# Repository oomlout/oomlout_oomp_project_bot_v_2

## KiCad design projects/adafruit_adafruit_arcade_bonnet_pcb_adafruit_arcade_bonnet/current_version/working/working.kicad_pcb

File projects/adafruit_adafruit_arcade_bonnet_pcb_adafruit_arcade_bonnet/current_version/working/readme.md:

# adafruit_arcade_bonnet_pcb
 
## summary 
* id: adafruit_adafruit_arcade_bonnet_pcb_adafruit_arcade_bonnet
* user: adafruit
* name: adafruit_arcade_bonnet_pcb
* board: adafruit_arcade_bonnet
* repo: https://github.com/adafruit/Adafruit-Arcade-Bonnet-PCB

* src_file_repo_sch: 
* src_file_repo_sch_link: https://github.com/adafruit/Adafruit-Arcade-Bonnet-PCB/tree/master/
* full details link: https://github.com/oomlout/oomlout_oomp_project_bot_v_2/tree/main/projects/adafruit_adafruit_arcade_bonnet_pcb_adafruit_arcade_bonnet/current_version/working  

## schematic  
  
[schematic (pdf)](working_schematic.pdf) 

## pcb  

[board (pdf)](working.pdf)  

## working_bom
| Id | Designator | Footprint | Quantity | Designation | Supplier and ref |  | None | 
| --- | --- | --- | --- | --- | --- | --- | --- | 
| 1 | U$11 | PCBFEAT-REV-040 | 1 |  |  |  | [''] | 
| 2 | B4,B3,B0,B5,B2,B1 | JST-XH-2-SM4 | 6 | CON_JST_XH_2PIN-SM4 |  |  | [''] | 
| 3 | R3,R2 | 0805-NO | 2 | 10K |  |  | [''] | 
| 4 | U1 | QFN16_3MM | 1 | MAX98357A |  |  | [''] | 
| 5 | JP8,JP9,JP10,JP7,JP4,JP6 | 1X02_OVAL | 6 |  |  |  | [''] | 
| 6 | RPI1 | PI_BONNET | 1 | RASPBERRYPI_BPLUS_PHAT |  |  | [''] | 
| 7 | R4 | 0603-NO | 1 | 1M |  |  | [''] | 
| 8 | JP2,JP3 | 1X03_ROUND | 2 |  |  |  | [''] | 
| 9 | IC1 | QFN28-ML_6X6MM | 1 | MCP23017ML |  |  | [''] | 
| 10 | SPKR0 | TERMBLOCK_1X2-3.5MM | 1 | 3.5mm |  |  | [''] | 
| 11 | FID2,FID3 | FIDUCIAL_1MM | 2 | FIDUCIAL" |  |  | [''] | 
| 12 | R1 | 0805_10MGAP | 1 | 10K |  |  | [''] | 
| 13 | JP1 | 1X04_OVAL | 1 |  |  |  | [''] | 
| 14 | D1 | CHIPLED_0805_NOOUTLINE | 1 | red |  |  | [''] | 
| 15 | R5 | 0603-NO | 1 | 1K |  |  | [''] | 
| 16 | IC2 | TSSOP14 | 1 | LM339P |  |  | [''] | 
| 17 | U$19 | BONNET_ARCADE_REVB_TOP | 1 |  |  |  | [''] | 
| 18 | C2 | 0805-NO | 1 | 10uF |  |  | [''] | 
| 19 | JOY1 | 1X05_OVAL | 1 |  |  |  | [''] | 
| 20 | C1 | 0603-NO | 1 | 0.1uF |  |  | [''] | 
| 21 | CONN1 | 1X25_ROUND_70MIL | 1 | HEADER-1X25 |  |  | [''] | 
| 22 | SJ1 | SOLDERJUMPER_2WAY_OPEN_NOPASTE | 1 | ADDR |  |  | [''] | 
| 23 | U$20 | BONNET_ARCADE_REVB_BOT | 1 |  |  |  | [''] | 
| 24 | SJ2 | SOLDERJUMPER_CLOSEDWIRE | 1 |  |  |  | [''] | 

## bom_schematic
| Ref | Qnty | Value | Cmp name | Footprint | Description | Vendor | DNP | 
| --- | --- | --- | --- | --- | --- | --- | --- | 
| B0, B1, B2, B3, B4, B5 | 6 | CON_JST_XH_2PIN-SM4 | CON_JST_XH_2PIN-SM4 | working:JST-XH-2-SM4 |  |  |  | 
| C1 | 1 | 0.1uF | CAP_CERAMIC0603_NO | working:0603-NO |  |  |  | 
| C2 | 1 | 10uF | CAP_CERAMIC0805-NOOUTLINE | working:0805-NO |  |  |  | 
| CONN1 | 1 | HEADER-1X25 | HEADER-1X25 | working:1X25_ROUND_70MIL |  |  |  | 
| D1 | 1 | red | LED0805_NOOUTLINE | working:CHIPLED_0805_NOOUTLINE |  |  |  | 
| FID2, FID3 | 2 | FIDUCIAL"" | FIDUCIAL{dblquote}{dblquote} | working:FIDUCIAL_1MM |  |  |  | 
| IC1 | 1 | MCP23017ML | MCP23017ML | working:QFN28-ML_6X6MM |  |  |  | 
| IC2 | 1 | LM339P | LM339P | working:TSSOP14 |  |  |  | 
| JOY1 | 1 | HEADER-1X5 | HEADER-1X5 | working:1X05_OVAL |  |  |  | 
| JP1 | 1 | HEADER-1X4 | HEADER-1X4 | working:1X04_OVAL |  |  |  | 
| JP2, JP3 | 2 | HEADER-1X3ROUND | HEADER-1X3ROUND | working:1X03_ROUND |  |  |  | 
| JP4, JP6, JP7, JP8, JP9, JP10 | 6 | HEADER-1X2 | HEADER-1X2 | working:1X02_OVAL |  |  |  | 
| R1 | 1 | 10K | RESISTOR0805_10MGAP | working:0805_10MGAP |  |  |  | 
| R2, R3 | 2 | 10K | RESISTOR0805_NOOUTLINE | working:0805-NO |  |  |  | 
| R4 | 1 | 1M | RESISTOR_0603_NOOUT | working:0603-NO |  |  |  | 
| R5 | 1 | 1K | RESISTOR_0603_NOOUT | working:0603-NO |  |  |  | 
| RPI1 | 1 | RASPBERRYPI_BPLUS_PHAT | RASPBERRYPI_BPLUS_PHAT | working:PI_BONNET |  |  |  | 
| SJ1 | 1 | ADDR | SOLDERJUMPER_2WAY | working:SOLDERJUMPER_2WAY_OPEN_NOPASTE |  |  |  | 
| SJ2 | 1 | SOLDERJUMPERCLOSED | SOLDERJUMPERCLOSED | working:SOLDERJUMPER_CLOSEDWIRE |  |  |  | 
| SPKR0 | 1 | 3.5mm | TERMBLOCK_1X2 | working:TERMBLOCK_1X2-3.5MM |  |  |  | 
| U1 | 1 | MAX98357A | AUDIOAMP_MAX98357 | working:QFN16_3MM |  |  |  |

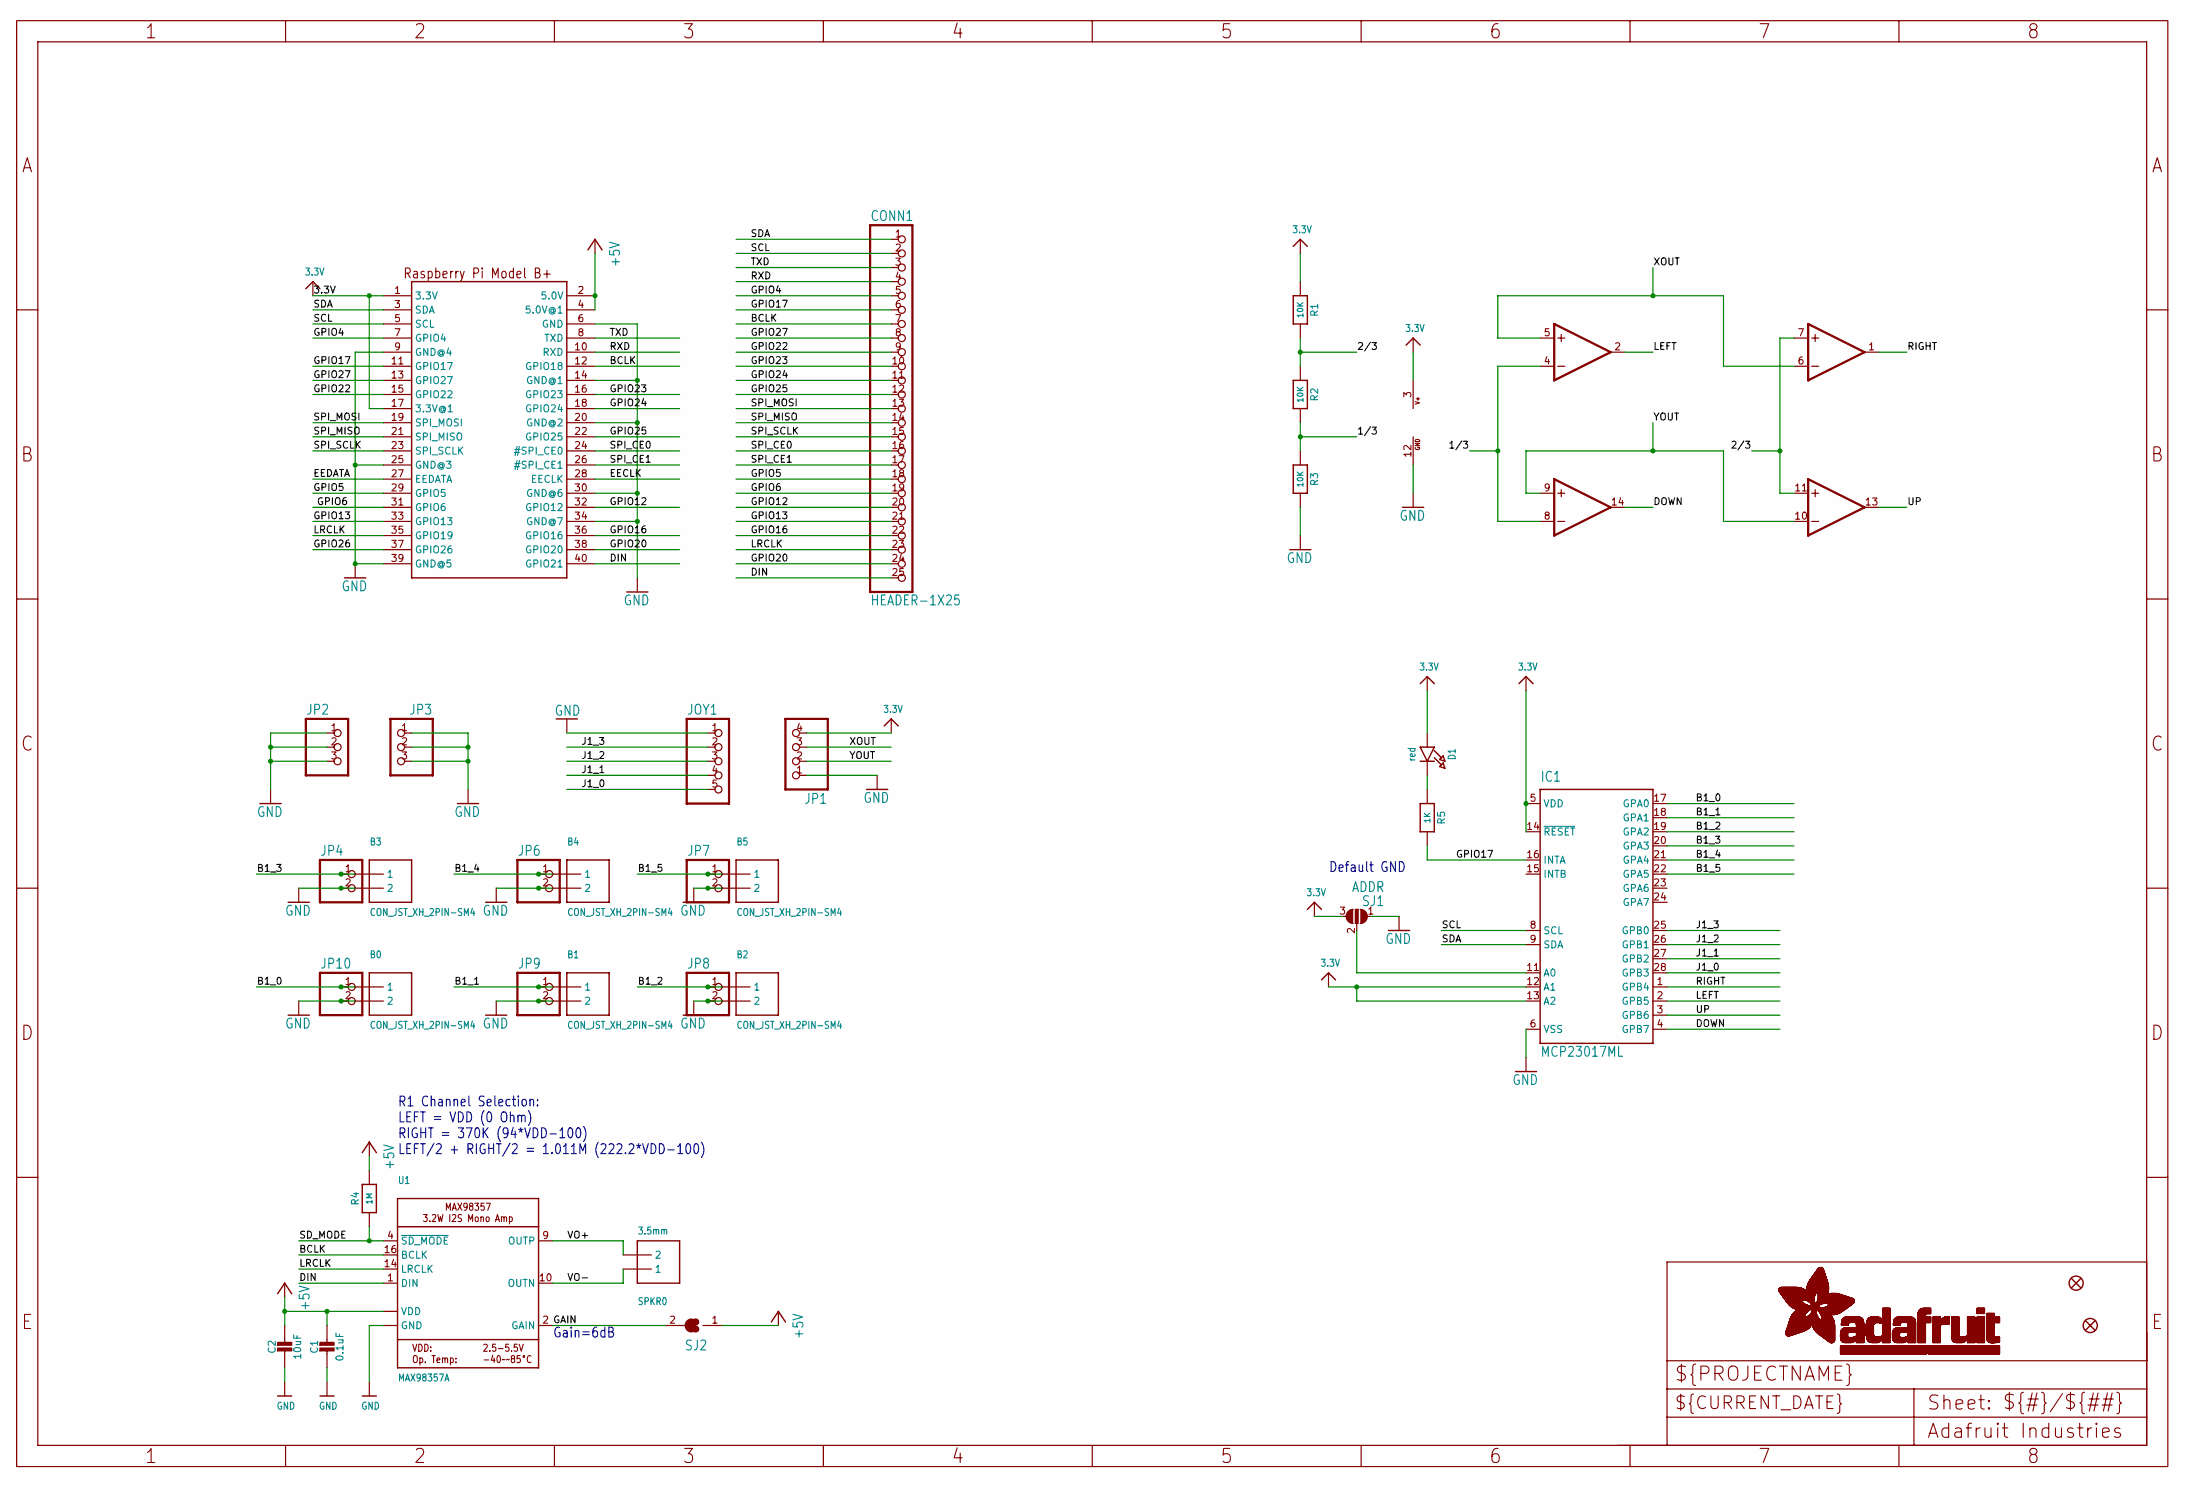
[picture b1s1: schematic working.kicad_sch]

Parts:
B0, B1, B2, B3, B4, B5: CON_JST_XH_2PIN-SM4; JST-XH-2-SM4
C1: 0.1uF; 0603-NO
C2: 10uF; 0805-NO
CONN1: HEADER-1X25; 1X25_ROUND_70MIL
D1: red; CHIPLED_0805_NOOUTLINE
FID2, FID3: FIDUCIAL""; FIDUCIAL_1MM
IC1: MCP23017ML; QFN28-ML_6X6MM; MPN MCP23017-E/SS
IC2: LM339P; TSSOP14
JOY1: HEADER-1X5; 1X05_OVAL
JP1: HEADER-1X4; 1X04_OVAL
JP2, JP3: HEADER-1X3ROUND; 1X03_ROUND
JP4, JP6, JP7, JP8, JP9, JP10: HEADER-1X2; 1X02_OVAL
R1: 10K; 0805_10MGAP
R2, R3: 10K; 0805-NO
R4: 1M; 0603-NO
R5: 1K; 0603-NO
RPI1: RASPBERRYPI_BPLUS_PHAT; PI_BONNET
SJ1: ADDR; SOLDERJUMPER_2WAY_OPEN_NOPASTE
SJ2: SOLDERJUMPERCLOSED; SOLDERJUMPER_CLOSEDWIRE
SPKR0: 3.5mm; TERMBLOCK_1X2-3.5MM
U1: MAX98357A; QFN16_3MM

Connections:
1/3: IC2.4 (-IN), IC2.8 (-IN), R2.2, R3.1
2/3: IC2.7 (+IN), IC2.11 (+IN), R1.2, R2.1
3.3V: D1.A, IC1.5 (VDD), IC1.12 (A1), IC1.13 (A2), IC1.14 (~RESET), IC2.3 (V+), JP1.4, R1.1, RPI1.1 (3.3V), RPI1.17 (3.3V@1), SJ1.3
+5V: C1.1, C2.1, R4.2, RPI1.2 (5.0V), RPI1.4 (5.0V@1), SJ2.1, U1.7 (VDD), U1.8 (VDD)
B1_0: B0.1, IC1.17 (GPA0), JP10.1
B1_1: B1.1, IC1.18 (GPA1), JP9.1
B1_2: B2.1, IC1.19 (GPA2), JP8.1
B1_3: B3.1, IC1.20 (GPA3), JP4.1
B1_4: B4.1, IC1.21 (GPA4), JP6.1
B1_5: B5.1, IC1.22 (GPA5), JP7.1
BCLK: CONN1.7, RPI1.12 (GPIO18), U1.16 (BCLK)
DIN: CONN1.25, RPI1.40 (GPIO21), U1.1 (DIN)
DOWN: IC1.4 (GPB7), IC2.14 (OUT)
EECLK: RPI1.28 (EECLK)
EEDATA: RPI1.27 (EEDATA)
GAIN: SJ2.2, U1.2 (GAIN)
GND: B0.2, B1.2, B2.2, B3.2, B4.2, B5.2, C1.2, C2.2, IC1.6 (VSS), IC2.12 (GND), JOY1.1, JP1.1, JP2.1, JP2.2, JP2.3, JP3.1, JP3.2, JP3.3, JP4.2, JP6.2, JP7.2, JP8.2, JP9.2, JP10.2, R3.2, RPI1.6 (GND), RPI1.9 (GND@4), RPI1.14 (GND@1), RPI1.20 (GND@2), RPI1.25 (GND@3), RPI1.30 (GND@6), RPI1.34 (GND@7), RPI1.39 (GND@5), SJ1.1, U1.3 (GND), U1.11 (GND), U1.15 (GND), U1.THERMAL (GND)
GPIO4: CONN1.5, RPI1.7 (GPIO4)
GPIO5: CONN1.18, RPI1.29 (GPIO5)
GPIO6: CONN1.19, RPI1.31 (GPIO6)
GPIO12: CONN1.20, RPI1.32 (GPIO12)
GPIO13: CONN1.21, RPI1.33 (GPIO13)
GPIO16: CONN1.22, RPI1.36 (GPIO16)
GPIO17: CONN1.6, IC1.16 (INTA), R5.2, RPI1.11 (GPIO17)
GPIO20: CONN1.24, RPI1.38 (GPIO20)
GPIO22: CONN1.9, RPI1.15 (GPIO22)
GPIO23: CONN1.10, RPI1.16 (GPIO23)
GPIO24: CONN1.11, RPI1.18 (GPIO24)
GPIO25: CONN1.12, RPI1.22 (GPIO25)
GPIO26: RPI1.37 (GPIO26)
GPIO27: CONN1.8, RPI1.13 (GPIO27)
J1_0: IC1.28 (GPB3), JOY1.5
J1_1: IC1.27 (GPB2), JOY1.4
J1_2: IC1.26 (GPB1), JOY1.3
J1_3: IC1.25 (GPB0), JOY1.2
LEFT: IC1.2 (GPB5), IC2.2 (OUT)
LRCLK: CONN1.23, RPI1.35 (GPIO19), U1.14 (LRCLK)
unnamed: IC1.11 (A0), SJ1.2
unnamed: D1.C, R5.1
RIGHT: IC1.1 (GPB4), IC2.1 (OUT)
RXD: CONN1.4, RPI1.10 (RXD)
SCL: CONN1.2, IC1.8 (SCL), RPI1.5 (SCL)
SDA: CONN1.1, IC1.9 (SDA), RPI1.3 (SDA)
SD_MODE: R4.1, U1.4 (~SD_MODE)
SPI_CE0: CONN1.16, RPI1.24 (#SPI_CE0)
SPI_CE1: CONN1.17, RPI1.26 (#SPI_CE1)
SPI_MISO: CONN1.14, RPI1.21 (SPI_MISO)
SPI_MOSI: CONN1.13, RPI1.19 (SPI_MOSI)
SPI_SCLK: CONN1.15, RPI1.23 (SPI_SCLK)
TXD: CONN1.3, RPI1.8 (TXD)
UP: IC1.3 (GPB6), IC2.13 (OUT)
VO+: SPKR0.2, U1.9 (OUTP)
VO-: SPKR0.1, U1.10 (OUTN)
XOUT: IC2.5 (+IN), IC2.6 (-IN), JP1.3
YOUT: IC2.9 (+IN), IC2.10 (-IN), JP1.2

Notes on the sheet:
Default GND
R1 Channel Selection: LEFT = VDD (0 Ohm) RIGHT = 370K (94*VDD-100) LEFT/2 + RIGHT/2 = 1.011M (222.2*VDD-100)
Gain=6dB

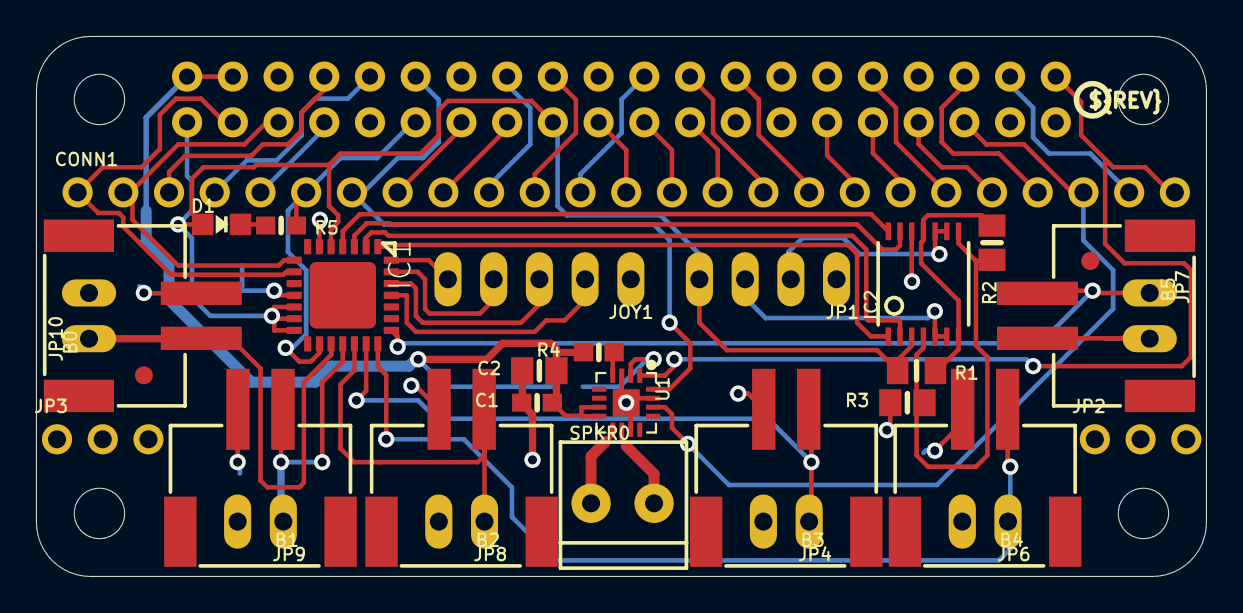
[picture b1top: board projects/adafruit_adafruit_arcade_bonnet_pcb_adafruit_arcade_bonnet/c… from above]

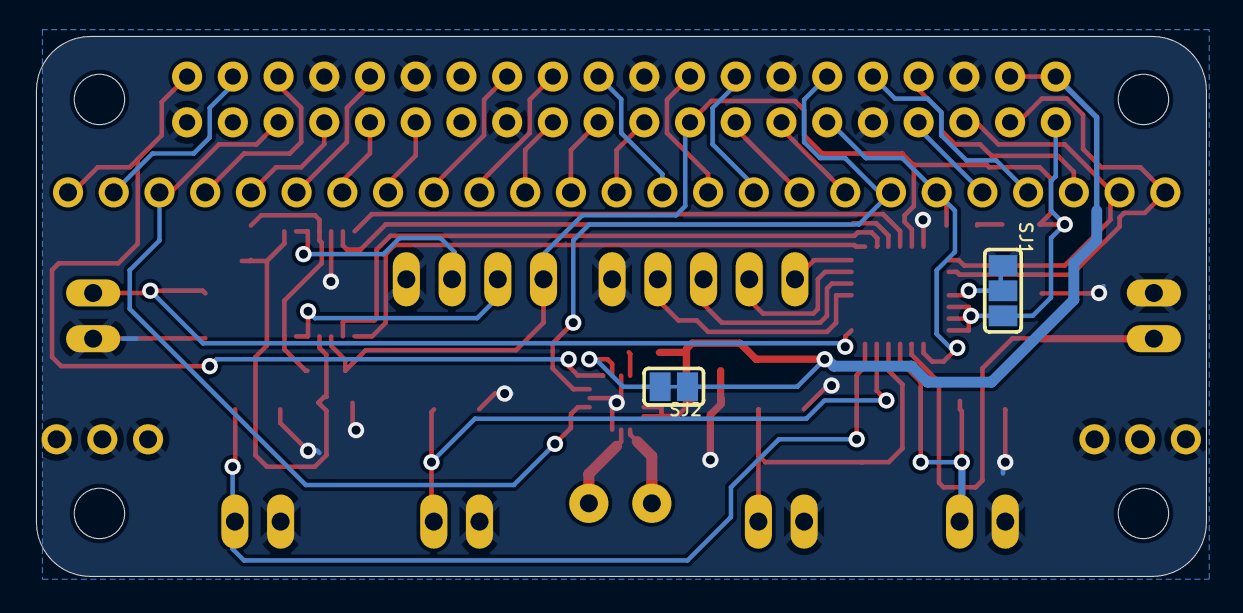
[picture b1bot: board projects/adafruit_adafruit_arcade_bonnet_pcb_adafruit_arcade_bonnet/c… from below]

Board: 2 copper layers, 65.0 x 30.0 mm, 37 parts (3 on the bottom side), 52 nets.

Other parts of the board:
U$11: PCBFEAT-REV-040
U$19: BONNET_ARCADE_REVB_TOP
U$20: BONNET_ARCADE_REVB_BOT

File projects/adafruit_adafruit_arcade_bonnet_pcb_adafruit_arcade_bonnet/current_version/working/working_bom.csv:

"Id";"Designator";"Footprint";"Quantity";"Designation";"Supplier and ref";
1;"U$11";"PCBFEAT-REV-040";1;"";;;
2;"B4,B3,B0,B5,B2,B1";"JST-XH-2-SM4";6;"CON_JST_XH_2PIN-SM4";;;
3;"R3,R2";"0805-NO";2;"10K";;;
4;"U1";"QFN16_3MM";1;"MAX98357A";;;
5;"JP8,JP9,JP10,JP7,JP4,JP6";"1X02_OVAL";6;"";;;
6;"RPI1";"PI_BONNET";1;"RASPBERRYPI_BPLUS_PHAT";;;
7;"R4";"0603-NO";1;"1M";;;
8;"JP2,JP3";"1X03_ROUND";2;"";;;
9;"IC1";"QFN28-ML_6X6MM";1;"MCP23017ML";;;
10;"SPKR0";"TERMBLOCK_1X2-3.5MM";1;"3.5mm";;;
11;"FID2,FID3";"FIDUCIAL_1MM";2;"FIDUCIAL""";;;
12;"R1";"0805_10MGAP";1;"10K";;;
13;"JP1";"1X04_OVAL";1;"";;;
14;"D1";"CHIPLED_0805_NOOUTLINE";1;"red";;;
15;"R5";"0603-NO";1;"1K";;;
16;"IC2";"TSSOP14";1;"LM339P";;;
17;"U$19";"BONNET_ARCADE_REVB_TOP";1;"";;;
18;"C2";"0805-NO";1;"10uF";;;
19;"JOY1";"1X05_OVAL";1;"";;;
20;"C1";"0603-NO";1;"0.1uF";;;
21;"CONN1";"1X25_ROUND_70MIL";1;"HEADER-1X25";;;
22;"SJ1";"SOLDERJUMPER_2WAY_OPEN_NOPASTE";1;"ADDR";;;
23;"U$20";"BONNET_ARCADE_REVB_BOT";1;"";;;
24;"SJ2";"SOLDERJUMPER_CLOSEDWIRE";1;"";;;

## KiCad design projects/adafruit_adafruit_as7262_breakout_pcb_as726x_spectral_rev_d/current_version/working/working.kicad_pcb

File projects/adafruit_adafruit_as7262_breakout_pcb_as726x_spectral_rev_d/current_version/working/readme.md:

# adafruit_as7262_breakout_pcb
 
## summary 
* id: adafruit_adafruit_as7262_breakout_pcb_as726x_spectral_rev_d
* user: adafruit
* name: adafruit_as7262_breakout_pcb
* board: as726x_spectral_rev_d
* repo: https://github.com/adafruit/Adafruit-AS7262-Breakout-PCB

* src_file_repo_sch: 
* src_file_repo_sch_link: https://github.com/adafruit/Adafruit-AS7262-Breakout-PCB/tree/master/
* full details link: https://github.com/oomlout/oomlout_oomp_project_bot_v_2/tree/main/projects/adafruit_adafruit_as7262_breakout_pcb_as726x_spectral_rev_d/current_version/working  

## schematic  
  
[schematic (pdf)](working_schematic.pdf) 

## pcb  

[board (pdf)](working.pdf)  

## working_bom
| Id | Designator | Footprint | Quantity | Designation | Supplier and ref |  | None | 
| --- | --- | --- | --- | --- | --- | --- | --- | 
| 1 | U$2,U$22,U$3,U$23 | MOUNTINGHOLE_2.5_PLATED | 4 | MOUNTINGHOLE2.5 |  |  | [''] | 
| 2 | U$25 | SYMBOL_PLUS | 1 |  |  |  | [''] | 
| 3 | R2 | 0805-NO | 1 | 10K |  |  | [''] | 
| 4 | D1 | EVERLIGHT_45-21 | 1 | L130-5780001400001 |  |  | [''] | 
| 5 | U2 | AS726X_LGA20 | 1 | AS7262-BLGT |  |  | [''] | 
| 6 | R8 | RESPACK_4X0603_NO | 1 | 10k |  |  | [''] | 
| 7 | EXT_LED0 | 1X02_ROUND | 1 |  |  |  | [''] | 
| 8 | C3,C1,C2 | 0805-NO | 3 | 10uF |  |  | [''] | 
| 9 | UART0 | SOLDERJUMPER_ARROW_NOPASTE | 1 |  |  |  | [''] | 
| 10 | R7 | 0603-NO | 1 | 10K |  |  | [''] | 
| 11 | C4,C5 | 0603-NO | 2 | 0.1uF |  |  | [''] | 
| 12 | Q3 | SOT363 | 1 | BSS138 |  |  | [''] | 
| 13 | D2 | CHIPLED_0805_NOOUTLINE | 1 | GREEN |  |  | [''] | 
| 14 | U3 | SOT23-5 | 1 | MIC5225-3.3 |  |  | [''] | 
| 15 | U1 | SOIC8_150MIL | 1 | AT25SF041-SSHD-B |  |  | [''] | 
| 16 | FID3,FID2 | FIDUCIAL_1MM | 2 | FIDUCIAL_1MM |  |  | [''] | 
| 17 | JP2,FTDI1 | 1X07_ROUND | 2 |  |  |  | [''] | 
| 18 | U$26 | SYMBOL_MINUS | 1 |  |  |  | [''] | 
| 19 | D3 | SOD-323 | 1 | IN4148 |  |  | [''] | 
| 20 | U$21 | ADAFRUIT_2.5MM | 1 |  |  |  | [''] | 
| 21 | TP1,TP3,TP2,TP4 | TP15R | 4 | PTR1TP15R |  |  | [''] | 
| 22 | U$9 | ADAFRUIT_5MM | 1 |  |  |  | [''] | 
| 23 | LED0 | SOLDERJUMPER_CLOSEDWIRE | 1 |  |  |  | [''] | 

## bom_schematic
| Ref | Qnty | Value | Cmp name | Footprint | Description | Vendor | DNP | 
| --- | --- | --- | --- | --- | --- | --- | --- | 
| C1, C2, C3 | 3 | 10uF | CAP_CERAMIC0805-NOOUTLINE | working:0805-NO |  |  |  | 
| C4, C5 | 2 | 0.1uF | CAP_CERAMIC0603_NO | working:0603-NO |  |  |  | 
| D1 | 1 | L130-5780001400001 | LEDEV45-21 | working:EVERLIGHT_45-21 |  |  |  | 
| D2 | 1 | GREEN | LED0805_NOOUTLINE | working:CHIPLED_0805_NOOUTLINE |  |  |  | 
| D3 | 1 | IN4148 | DIODESOD-323 | working:SOD-323 |  |  |  | 
| EXT_LED0 | 1 | HEADER-1X2ROUND | HEADER-1X2ROUND | working:1X02_ROUND |  |  |  | 
| FID2, FID3 | 2 | FIDUCIAL_1MM | FIDUCIAL_1MM | working:FIDUCIAL_1MM |  |  |  | 
| FTDI1 | 1 | HEADER-1X7ROUND | HEADER-1X7ROUND | working:1X07_ROUND |  |  |  | 
| JP2 | 1 | HEADER-1X7ROUND | HEADER-1X7ROUND | working:1X07_ROUND |  |  |  | 
| LED0 | 1 | SOLDERJUMPERCLOSED | SOLDERJUMPERCLOSED | working:SOLDERJUMPER_CLOSEDWIRE |  |  |  | 
| Q3 | 1 | BSS138 | MOSFET-N_DUAL | working:SOT363 |  |  |  | 
| R2 | 1 | 10K | RESISTOR0805_NOOUTLINE | working:0805-NO |  |  |  | 
| R7 | 1 | 10K | microbuilder_09_Nov_2015_RESISTOR_0603_NOOUT | working:0603-NO |  |  |  | 
| R8 | 1 | 10k | RESISTOR_4PACK_NO | working:RESPACK_4X0603_NO |  |  |  | 
| TP1, TP2, TP3, TP4 | 4 | PTR1TP15R | PTR1TP15R | working:TP15R |  |  |  | 
| U1 | 1 | AT25SF041-SSHD-B | SPIFLASH_SOIC8 | working:SOIC8_150MIL |  |  |  | 
| U2 | 1 | AS7262-BLGT | AS726X_SPECTRAL | working:AS726X_LGA20 |  |  |  | 
| U3 | 1 | MIC5225-3.3 | VREG_SOT23-5 | working:SOT23-5 |  |  |  | 
| U$2, U$3, U$22, U$23 | 4 | MOUNTINGHOLE2.5 | MOUNTINGHOLE2.5 | working:MOUNTINGHOLE_2.5_PLATED |  |  |  | 
| UART0 | 1 | SOLDERJUMPER | SOLDERJUMPER | working:SOLDERJUMPER_ARROW_NOPASTE |  |  |  | 

## mounting_holes
| x | y | package | value | ref | size | 
| --- | --- | --- | --- | --- | --- | 
| 22.86 | 0.0 | MOUNTINGHOLE_2.5_PLATED | MOUNTINGHOLE2.5 | U$2 | m3 | 
| 0.0 | 0.0 | MOUNTINGHOLE_2.5_PLATED | MOUNTINGHOLE2.5 | U$3 | m3 | 
| 22.86 | 20.32 | MOUNTINGHOLE_2.5_PLATED | MOUNTINGHOLE2.5 | U$22 | m3 | 
| 0.0 | 20.32 | MOUNTINGHOLE_2.5_PLATED | MOUNTINGHOLE2.5 | U$23 | m3 |

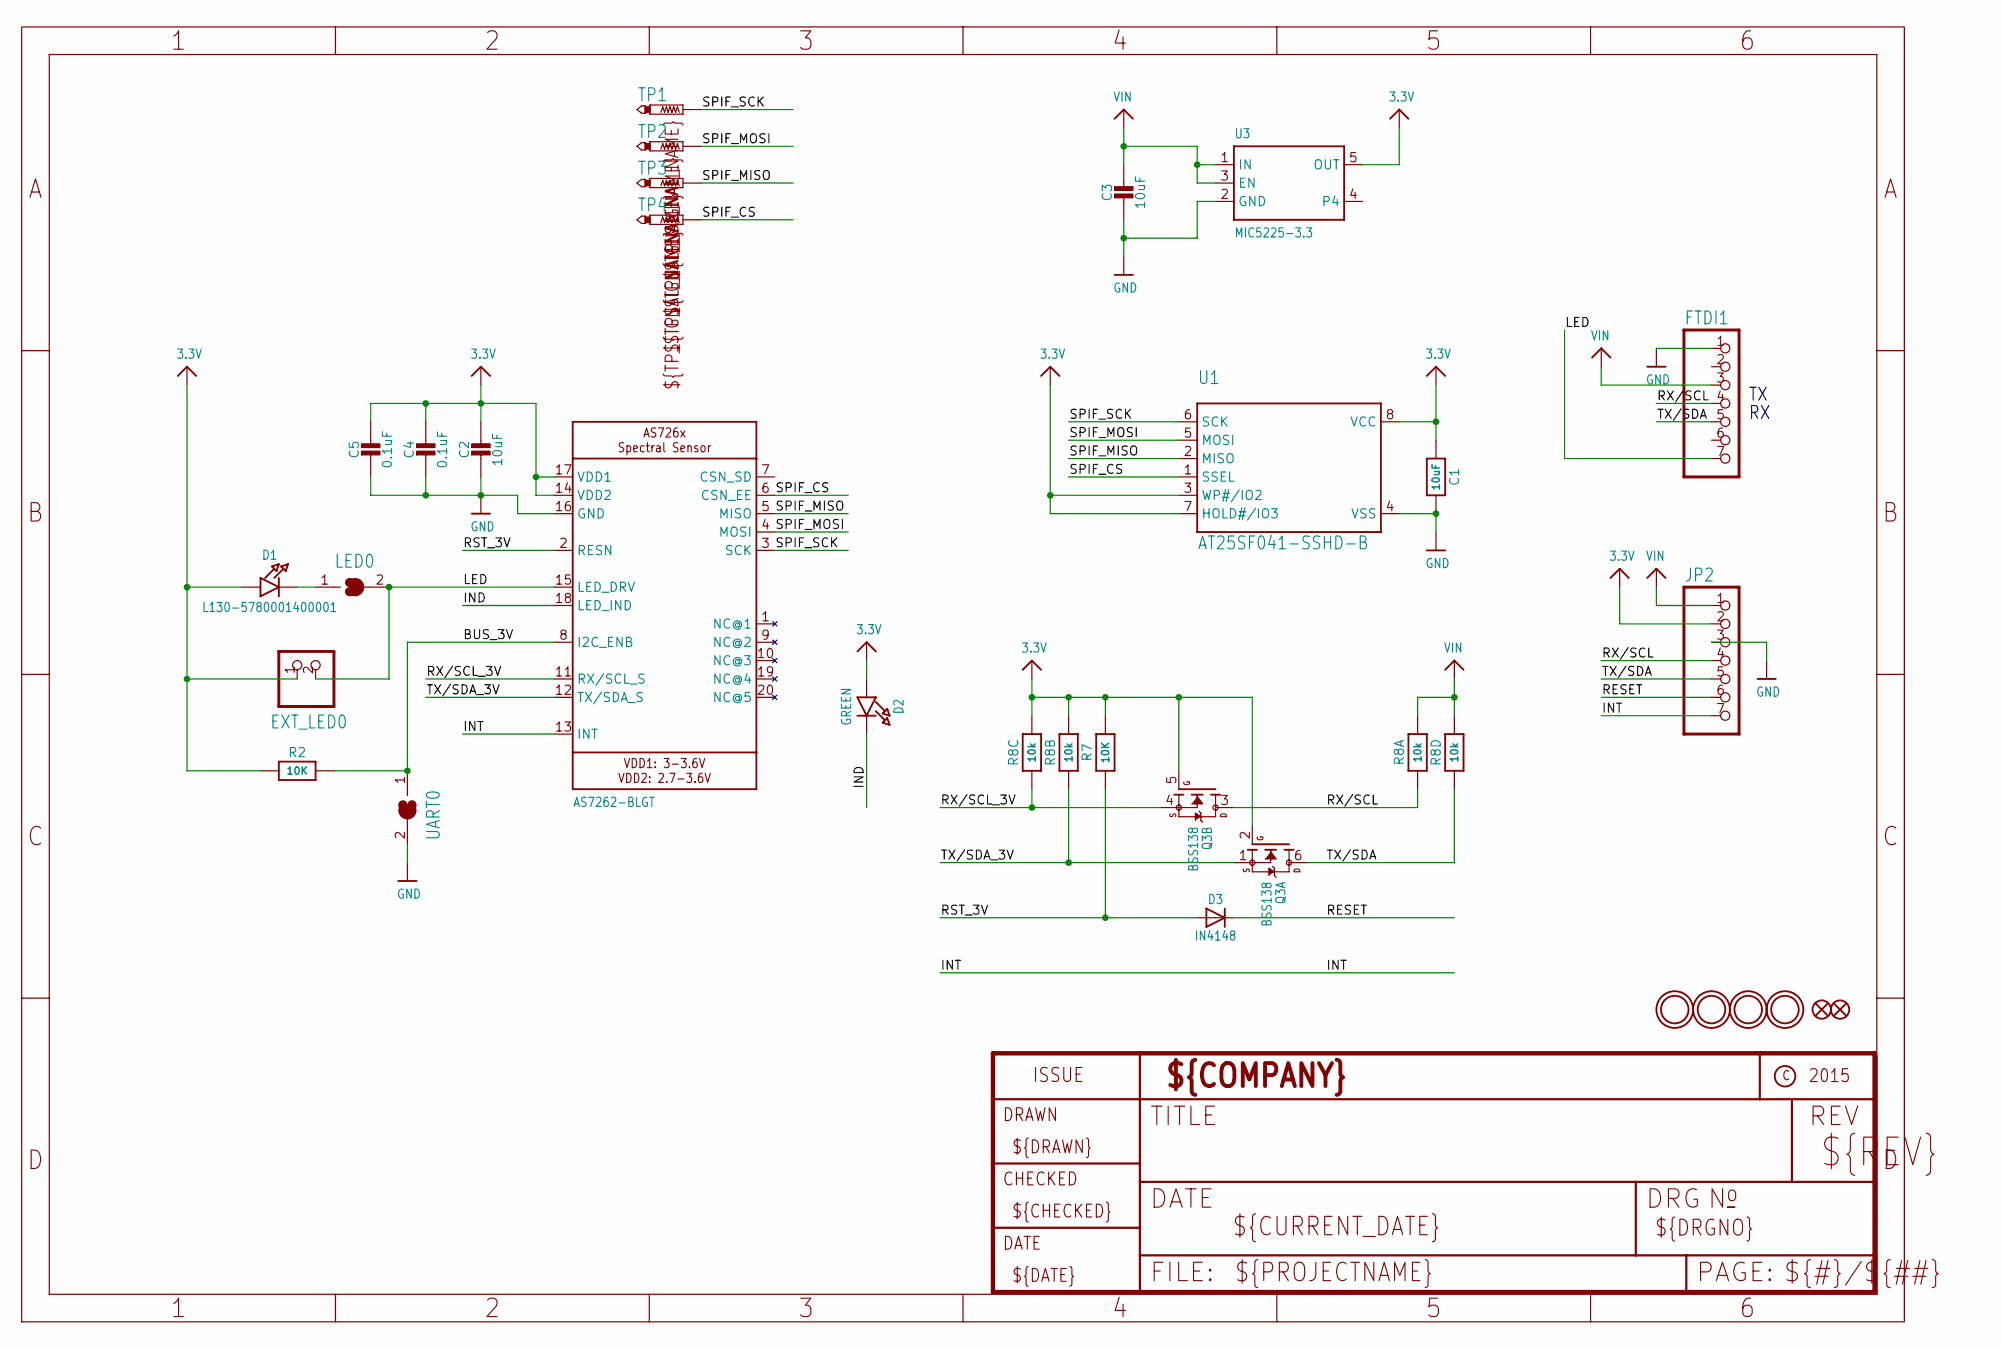
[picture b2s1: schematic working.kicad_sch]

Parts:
C1, C2, C3: 10uF; 0805-NO
C4, C5: 0.1uF; 0603-NO
D1: L130-5780001400001; EVERLIGHT_45-21
D2: GREEN; CHIPLED_0805_NOOUTLINE
D3: IN4148; SOD-323
EXT_LED0: HEADER-1X2ROUND; 1X02_ROUND
FID2, FID3: FIDUCIAL_1MM
FTDI1: HEADER-1X7ROUND; 1X07_ROUND
JP2: HEADER-1X7ROUND; 1X07_ROUND
LED0: SOLDERJUMPERCLOSED; SOLDERJUMPER_CLOSEDWIRE
Q3: BSS138; SOT363
R2: 10K; 0805-NO
R7: 10K; 0603-NO
R8: 10k; RESPACK_4X0603_NO
TP1, TP2, TP3, TP4: PTR1TP15R; TP15R
U1: AT25SF041-SSHD-B; SOIC8_150MIL
U2: AS7262-BLGT; AS726X_LGA20
U3: MIC5225-3.3; SOT23-5
U$2, U$3, U$22, U$23: MOUNTINGHOLE2.5; MOUNTINGHOLE_2.5_PLATED
UART0: SOLDERJUMPER; SOLDERJUMPER_ARROW_NOPASTE

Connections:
3.3V: C1.1, C2.1, C4.1, C5.1, D1.A, D2.A, EXT_LED0.1, JP2.2, Q3.2 (G), Q3.5 (G), R2.1, R7.2, R8.6 (2), R8.7 (2), U1.3 (WP#/IO2), U1.7 (HOLD#/IO3), U1.8 (VCC), U2.14 (VDD2), U2.17 (VDD1), U3.5 (OUT)
BUS_3V: R2.2, U2.8 (I2C_ENB), UART0.1
GND: C1.2, C2.2, C3.2, C4.2, C5.2, FTDI1.1, JP2.3, U1.4 (VSS), U2.16 (GND), U3.2 (GND), UART0.2
IND: D2.C, U2.18 (LED_IND)
INT: JP2.7, U2.13 (INT)
LED: EXT_LED0.2, FTDI1.7, LED0.2, U2.15 (LED_DRV)
unnamed: D1.K (C), LED0.1
RESET: D3.C, JP2.6
RST_3V: D3.A, R7.1, U2.2 (RESN)
RX/SCL: FTDI1.4, JP2.4, Q3.3 (D), R8.1
RX/SCL_3V: Q3.4 (S), R8.3 (1), U2.11 (RX/SCL_S)
SPIF_CS: TP4.TP, U1.1 (SSEL), U2.6 (CSN_EE)
SPIF_MISO: TP3.TP, U1.2 (MISO), U2.5 (MISO)
SPIF_MOSI: TP2.TP, U1.5 (MOSI), U2.4 (MOSI)
SPIF_SCK: TP1.TP, U1.6 (SCK), U2.3 (SCK)
TX/SDA: FTDI1.5, JP2.5, Q3.6 (D), R8.4 (1)
TX/SDA_3V: Q3.1 (S), R8.2 (1), U2.12 (TX/SDA_S)
VIN: C3.1, FTDI1.3, JP2.1, R8.5 (2), R8.8 (2), U3.1 (IN), U3.3 (EN)

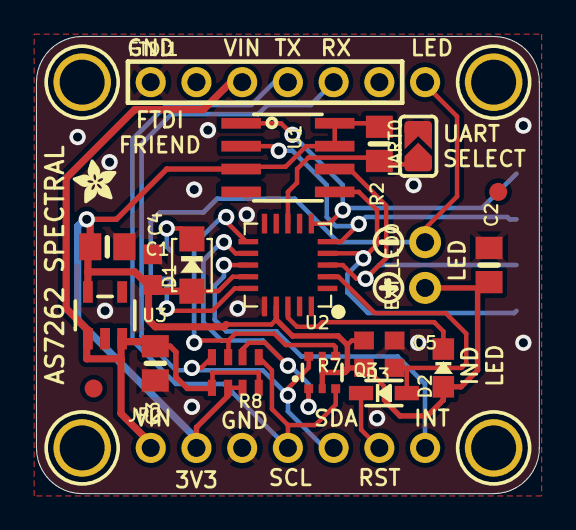
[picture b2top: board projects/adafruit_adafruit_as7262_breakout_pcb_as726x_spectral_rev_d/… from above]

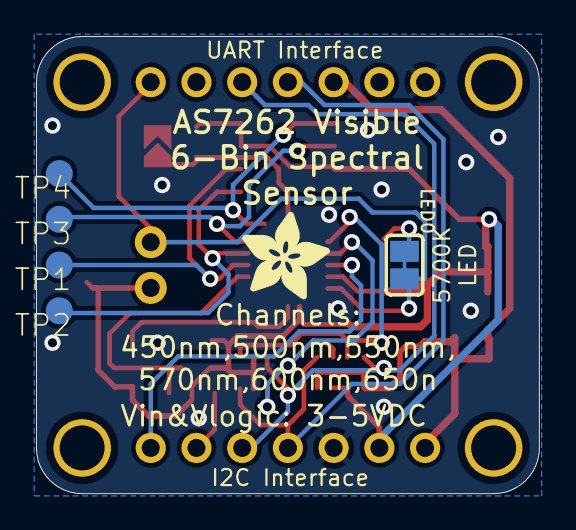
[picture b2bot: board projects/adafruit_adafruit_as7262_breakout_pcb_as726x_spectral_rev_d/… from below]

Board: 2 copper layers, 27.9 x 25.4 mm, 34 parts (6 on the bottom side), 18 nets.

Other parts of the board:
U$9: ADAFRUIT_5MM
U$21: ADAFRUIT_2.5MM
U$25: SYMBOL_PLUS
U$26: SYMBOL_MINUS

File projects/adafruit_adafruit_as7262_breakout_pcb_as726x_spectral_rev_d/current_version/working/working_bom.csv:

"Id";"Designator";"Footprint";"Quantity";"Designation";"Supplier and ref";
1;"U$2,U$22,U$3,U$23";"MOUNTINGHOLE_2.5_PLATED";4;"MOUNTINGHOLE2.5";;;
2;"U$25";"SYMBOL_PLUS";1;"";;;
3;"R2";"0805-NO";1;"10K";;;
4;"D1";"EVERLIGHT_45-21";1;"L130-5780001400001";;;
5;"U2";"AS726X_LGA20";1;"AS7262-BLGT";;;
6;"R8";"RESPACK_4X0603_NO";1;"10k";;;
7;"EXT_LED0";"1X02_ROUND";1;"";;;
8;"C3,C1,C2";"0805-NO";3;"10uF";;;
9;"UART0";"SOLDERJUMPER_ARROW_NOPASTE";1;"";;;
10;"R7";"0603-NO";1;"10K";;;
11;"C4,C5";"0603-NO";2;"0.1uF";;;
12;"Q3";"SOT363";1;"BSS138";;;
13;"D2";"CHIPLED_0805_NOOUTLINE";1;"GREEN";;;
14;"U3";"SOT23-5";1;"MIC5225-3.3";;;
15;"U1";"SOIC8_150MIL";1;"AT25SF041-SSHD-B";;;
16;"FID3,FID2";"FIDUCIAL_1MM";2;"FIDUCIAL_1MM";;;
17;"JP2,FTDI1";"1X07_ROUND";2;"";;;
18;"U$26";"SYMBOL_MINUS";1;"";;;
19;"D3";"SOD-323";1;"IN4148";;;
20;"U$21";"ADAFRUIT_2.5MM";1;"";;;
21;"TP1,TP3,TP2,TP4";"TP15R";4;"PTR1TP15R";;;
22;"U$9";"ADAFRUIT_5MM";1;"";;;
23;"LED0";"SOLDERJUMPER_CLOSEDWIRE";1;"";;;

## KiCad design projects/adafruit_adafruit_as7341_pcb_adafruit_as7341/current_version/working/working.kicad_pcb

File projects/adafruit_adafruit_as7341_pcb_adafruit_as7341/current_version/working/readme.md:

# adafruit_as7341_pcb
 
## summary 
* id: adafruit_adafruit_as7341_pcb_adafruit_as7341
* user: adafruit
* name: adafruit_as7341_pcb
* board: adafruit_as7341
* repo: https://github.com/adafruit/Adafruit-AS7341-PCB

* src_file_repo_sch: 
* src_file_repo_sch_link: https://github.com/adafruit/Adafruit-AS7341-PCB/tree/master/
* full details link: https://github.com/oomlout/oomlout_oomp_project_bot_v_2/tree/main/projects/adafruit_adafruit_as7341_pcb_adafruit_as7341/current_version/working  

## schematic  
  
[schematic (pdf)](working_schematic.pdf) 

## pcb  

[board (pdf)](working.pdf)  

## working_bom
| Id | Designator | Footprint | Quantity | Designation | Supplier and ref |  | None | 
| --- | --- | --- | --- | --- | --- | --- | --- | 
| 1 | U$17,U$19,U$1,U$21 | MOUNTINGHOLE_2.5_PLATED | 4 | MOUNTINGHOLE2.5 |  |  | [''] | 
| 2 | LED1 | KA-3528ASYC | 1 | EAHC2835WD6   |  |  | [''] | 
| 3 | C4,C3,C2 | 0805-NO | 3 | 10uF |  |  | [''] | 
| 4 | FID3,FID4 | FIDUCIAL_1MM | 2 | FIDUCIAL_1MM |  |  | [''] | 
| 5 | R2,R1 | 0603-NO | 2 | 10K |  |  | [''] | 
| 6 | D1 | CHIPLED_0603_NOOUTLINE | 1 | GREEN |  |  | [''] | 
| 7 | Q2 | SOT363 | 1 | BSS138 |  |  | [''] | 
| 8 | R3 | RESPACK_4X0603 | 1 | 10K |  |  | [''] | 
| 9 | CONN3,CONN4 | JST_SH4 | 2 | STEMMA_I2C_QT |  |  | [''] | 
| 10 | JP1 | 1X06_ROUND_70 | 1 |  |  |  | [''] | 
| 11 | X1 | AS7341 | 1 | AS7341 |  |  | [''] | 
| 12 | U1 | SOT23-6 | 1 | AP7312-3.3/1.8 |  |  | [''] | 
| 13 | U$22 | ADAFRUIT_3.5MM | 1 |  |  |  | [''] | 
| 14 | C1 | 0603-NO | 1 | 0.1uF |  |  | [''] | 
| 15 | U$31,U$30 | STEMMAQT | 2 |  |  |  | [''] | 
| 16 | U$25 | PCBFEAT-REV-040 | 1 |  |  |  | [''] | 

## bom_schematic
| Ref | Qnty | Value | Cmp name | Footprint | Description | Vendor | DNP | 
| --- | --- | --- | --- | --- | --- | --- | --- | 
| C1 | 1 | 0.1uF | CAP_CERAMIC0603_NO | working:0603-NO |  |  |  | 
| C2, C3, C4 | 3 | 10uF | CAP_CERAMIC0805-NOOUTLINE | working:0805-NO |  |  |  | 
| CONN3, CONN4 | 2 | STEMMA_I2C_QT | STEMMA_I2C_QT | working:JST_SH4 |  |  |  | 
| D1 | 1 | GREEN | LED0603_NOOUTLINE | working:CHIPLED_0603_NOOUTLINE |  |  |  | 
| FID3, FID4 | 2 | FIDUCIAL_1MM | FIDUCIAL_1MM | working:FIDUCIAL_1MM |  |  |  | 
| JP1 | 1 | HEADER-1X670MIL | HEADER-1X670MIL | working:1X06_ROUND_70 |  |  |  | 
| LED1 | 1 | EAHC2835WD6   | LEDKA-3528ASYC | working:KA-3528ASYC |  |  |  | 
| Q2 | 1 | BSS138 | MOSFET-N_DUAL | working:SOT363 |  |  |  | 
| R1, R2 | 2 | 10K | RESISTOR_0603_NOOUT | working:0603-NO |  |  |  | 
| R3 | 1 | 10K | RESISTOR_4PACK | working:RESPACK_4X0603 |  |  |  | 
| U1 | 1 | AP7312-3.3/1.8 | VREG_SOT23-6_DUALAP7312 | working:SOT23-6 |  |  |  | 
| U$1, U$17, U$19, U$21 | 4 | MOUNTINGHOLE2.5 | MOUNTINGHOLE2.5 | working:MOUNTINGHOLE_2.5_PLATED |  |  |  | 
| X1 | 1 | AS7341 | AS7341 | working:AS7341 |  |  |  | 

## mounting_holes
| x | y | package | value | ref | size | 
| --- | --- | --- | --- | --- | --- | 
| 0.0 | 12.7 | MOUNTINGHOLE_2.5_PLATED | MOUNTINGHOLE2.5 | U$1 | m3 | 
| 20.32 | 12.7 | MOUNTINGHOLE_2.5_PLATED | MOUNTINGHOLE2.5 | U$17 | m3 | 
| 0.0 | 0.0 | MOUNTINGHOLE_2.5_PLATED | MOUNTINGHOLE2.5 | U$19 | m3 | 
| 20.32 | 0.0 | MOUNTINGHOLE_2.5_PLATED | MOUNTINGHOLE2.5 | U$21 | m3 |

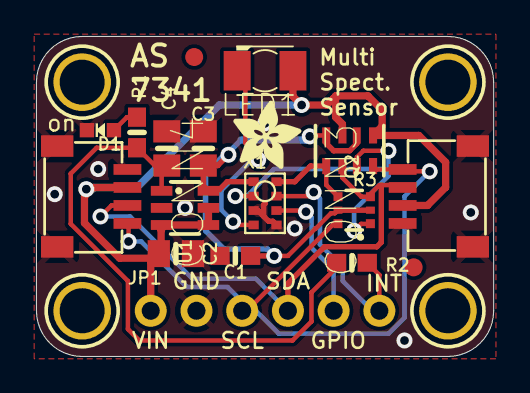
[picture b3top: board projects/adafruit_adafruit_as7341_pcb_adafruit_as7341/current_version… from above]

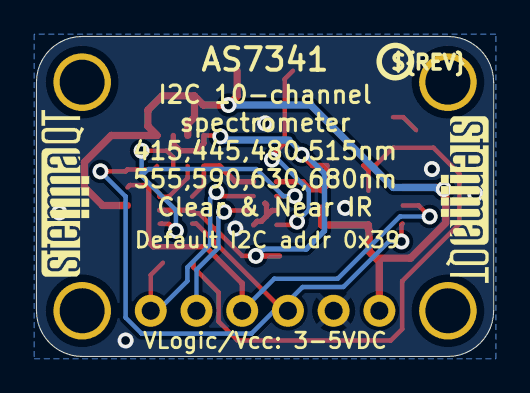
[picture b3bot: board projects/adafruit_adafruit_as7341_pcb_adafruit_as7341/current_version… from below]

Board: 2 copper layers, 25.4 x 17.8 mm, 25 parts (3 on the bottom side), 12 nets.

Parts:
C1: 0.1uF; 0603-NO
C2, C3, C4: 10uF; 0805-NO
CONN3, CONN4: STEMMA_I2C_QT; JST_SH4
D1: GREEN; CHIPLED_0603_NOOUTLINE
FID3, FID4: FIDUCIAL_1MM
JP1: 1X06_ROUND_70
LED1: EAHC2835WD6; KA-3528ASYC
Q2: BSS138; SOT363
R1, R2: 10K; 0603-NO
R3: 10K; RESPACK_4X0603
U1: AP7312-3.3/1.8; SOT23-6
U$1, U$17, U$19, U$21: MOUNTINGHOLE2.5; MOUNTINGHOLE_2.5_PLATED
U$22: ADAFRUIT_3.5MM
U$25: PCBFEAT-REV-040
U$30, U$31: STEMMAQT
X1: AS7341

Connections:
1.8V: C1.1, C3.1, Q2.2, Q2.5, R3.2, R3.4, U1.6, X1.1
3.3V: C4.1, R1.1, R2.1, U1.1
GND: C1.2, C2.2, C3.2, C4.2, CONN3.1, CONN3.MT1, CONN3.MT2, CONN4.1, CONN4.MT1, CONN4.MT2, D1.C, JP1.2, U1.2, X1.3, X1.5
GPIO: JP1.5, X1.6
INT: JP1.6, R2.2, X1.7
LDR: LED1.C, X1.4
unnamed: D1.A, R1.2
SCL: CONN3.4, CONN4.4, JP1.3, Q2.6, R3.8
SCL_2V: Q2.1, R3.7, X1.2
SDA: CONN3.3, CONN4.3, JP1.4, Q2.3, R3.6
SDA_2V: Q2.4, R3.5, X1.8
VCC: C2.1, CONN3.2, CONN4.2, JP1.1, LED1.A, R3.1, R3.3, U1.3, U1.4, U1.5

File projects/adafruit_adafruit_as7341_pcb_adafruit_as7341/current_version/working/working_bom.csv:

"Id";"Designator";"Footprint";"Quantity";"Designation";"Supplier and ref";
1;"U$17,U$19,U$1,U$21";"MOUNTINGHOLE_2.5_PLATED";4;"MOUNTINGHOLE2.5";;;
2;"LED1";"KA-3528ASYC";1;"EAHC2835WD6  ";;;
3;"C4,C3,C2";"0805-NO";3;"10uF";;;
4;"FID3,FID4";"FIDUCIAL_1MM";2;"FIDUCIAL_1MM";;;
5;"R2,R1";"0603-NO";2;"10K";;;
6;"D1";"CHIPLED_0603_NOOUTLINE";1;"GREEN";;;
7;"Q2";"SOT363";1;"BSS138";;;
8;"R3";"RESPACK_4X0603";1;"10K";;;
9;"CONN3,CONN4";"JST_SH4";2;"STEMMA_I2C_QT";;;
10;"JP1";"1X06_ROUND_70";1;"";;;
11;"X1";"AS7341";1;"AS7341";;;
12;"U1";"SOT23-6";1;"AP7312-3.3/1.8";;;
13;"U$22";"ADAFRUIT_3.5MM";1;"";;;
14;"C1";"0603-NO";1;"0.1uF";;;
15;"U$31,U$30";"STEMMAQT";2;"";;;
16;"U$25";"PCBFEAT-REV-040";1;"";;;

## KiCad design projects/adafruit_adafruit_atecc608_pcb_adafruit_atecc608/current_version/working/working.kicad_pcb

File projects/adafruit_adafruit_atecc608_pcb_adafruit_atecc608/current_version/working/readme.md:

# adafruit_atecc608_pcb
 
## summary 
* id: adafruit_adafruit_atecc608_pcb_adafruit_atecc608
* user: adafruit
* name: adafruit_atecc608_pcb
* board: adafruit_atecc608
* repo: https://github.com/adafruit/Adafruit-ATECC608-PCB

* src_file_repo_sch: 
* src_file_repo_sch_link: https://github.com/adafruit/Adafruit-ATECC608-PCB/tree/master/
* full details link: https://github.com/oomlout/oomlout_oomp_project_bot_v_2/tree/main/projects/adafruit_adafruit_atecc608_pcb_adafruit_atecc608/current_version/working  

## schematic  
  
[schematic (pdf)](working_schematic.pdf) 

## pcb  

[board (pdf)](working.pdf)  

## working_bom
| Id | Designator | Footprint | Quantity | Designation | Supplier and ref |  | None | 
| --- | --- | --- | --- | --- | --- | --- | --- | 
| 1 | U$12,U$11,U$14,U$15 | MOUNTINGHOLE_2.5_PLATED | 4 | MOUNTINGHOLE2.5 |  |  | [''] | 
| 2 | JP2 | 1X04_ROUND | 1 |  |  |  | [''] | 
| 3 | U$17 | ADAFRUIT_3.5MM | 1 |  |  |  | [''] | 
| 4 | FID4,FID3 | FIDUCIAL_1MM | 2 | FIDUCIAL_1MM |  |  | [''] | 
| 5 | ECC1 | SOIC8 | 1 | ATECC608 |  |  | [''] | 
| 6 | R3 | 0603-NO | 1 | 4.7K |  |  | [''] | 
| 7 | R4,R5 | 0603-NO | 2 | 10K |  |  | [''] | 
| 8 | C2 | 0805-NO | 1 | 10uF |  |  | [''] | 
| 9 | D1 | CHIPLED_0603_NOOUTLINE | 1 | GREEN |  |  | [''] | 
| 10 | CONN4,CONN3 | JST_SH4 | 2 | STEMMA_I2C_QT |  |  | [''] | 
| 11 | C1 | 0603-NO | 1 | 0.1uF |  |  | [''] | 
| 12 | U$20,U$19 | STEMMAQT | 2 |  |  |  | [''] | 
| 13 | U$18 | PCBFEAT-REV-040 | 1 |  |  |  | [''] | 

## bom_schematic
| Ref | Qnty | Value | Cmp name | Footprint | Description | Vendor | DNP | 
| --- | --- | --- | --- | --- | --- | --- | --- | 
| C1 | 1 | 0.1uF | CAP_CERAMIC0603_NO | working:0603-NO |  |  |  | 
| C2 | 1 | 10uF | CAP_CERAMIC0805-NOOUTLINE | working:0805-NO |  |  |  | 
| CONN3, CONN4 | 2 | STEMMA_I2C_QT | STEMMA_I2C_QT | working:JST_SH4 |  |  |  | 
| D1 | 1 | GREEN | LED0603_NOOUTLINE | working:CHIPLED_0603_NOOUTLINE |  |  |  | 
| ECC1 | 1 | ATECC108 | ATECC108 | working:SOIC8 |  |  |  | 
| FID3, FID4 | 2 | FIDUCIAL_1MM | FIDUCIAL_1MM | working:FIDUCIAL_1MM |  |  |  | 
| JP2 | 1 | HEADER-1X4ROUND | HEADER-1X4ROUND | working:1X04_ROUND |  |  |  | 
| R3 | 1 | 4.7K | RESISTOR_0603_NOOUT | working:0603-NO |  |  |  | 
| R4, R5 | 2 | 10K | RESISTOR_0603_NOOUT | working:0603-NO |  |  |  | 
| U$11, U$12, U$14, U$15 | 4 | MOUNTINGHOLE2.5 | MOUNTINGHOLE2.5 | working:MOUNTINGHOLE_2.5_PLATED |  |  |  | 

## mounting_holes
| x | y | package | value | ref | size | 
| --- | --- | --- | --- | --- | --- | 
| 0.0 | 12.7 | MOUNTINGHOLE_2.5_PLATED | MOUNTINGHOLE2.5 | U$11 | m3 | 
| 20.32 | 12.7 | MOUNTINGHOLE_2.5_PLATED | MOUNTINGHOLE2.5 | U$12 | m3 | 
| 0.0 | 0.0 | MOUNTINGHOLE_2.5_PLATED | MOUNTINGHOLE2.5 | U$14 | m3 | 
| 20.32 | 0.0 | MOUNTINGHOLE_2.5_PLATED | MOUNTINGHOLE2.5 | U$15 | m3 |

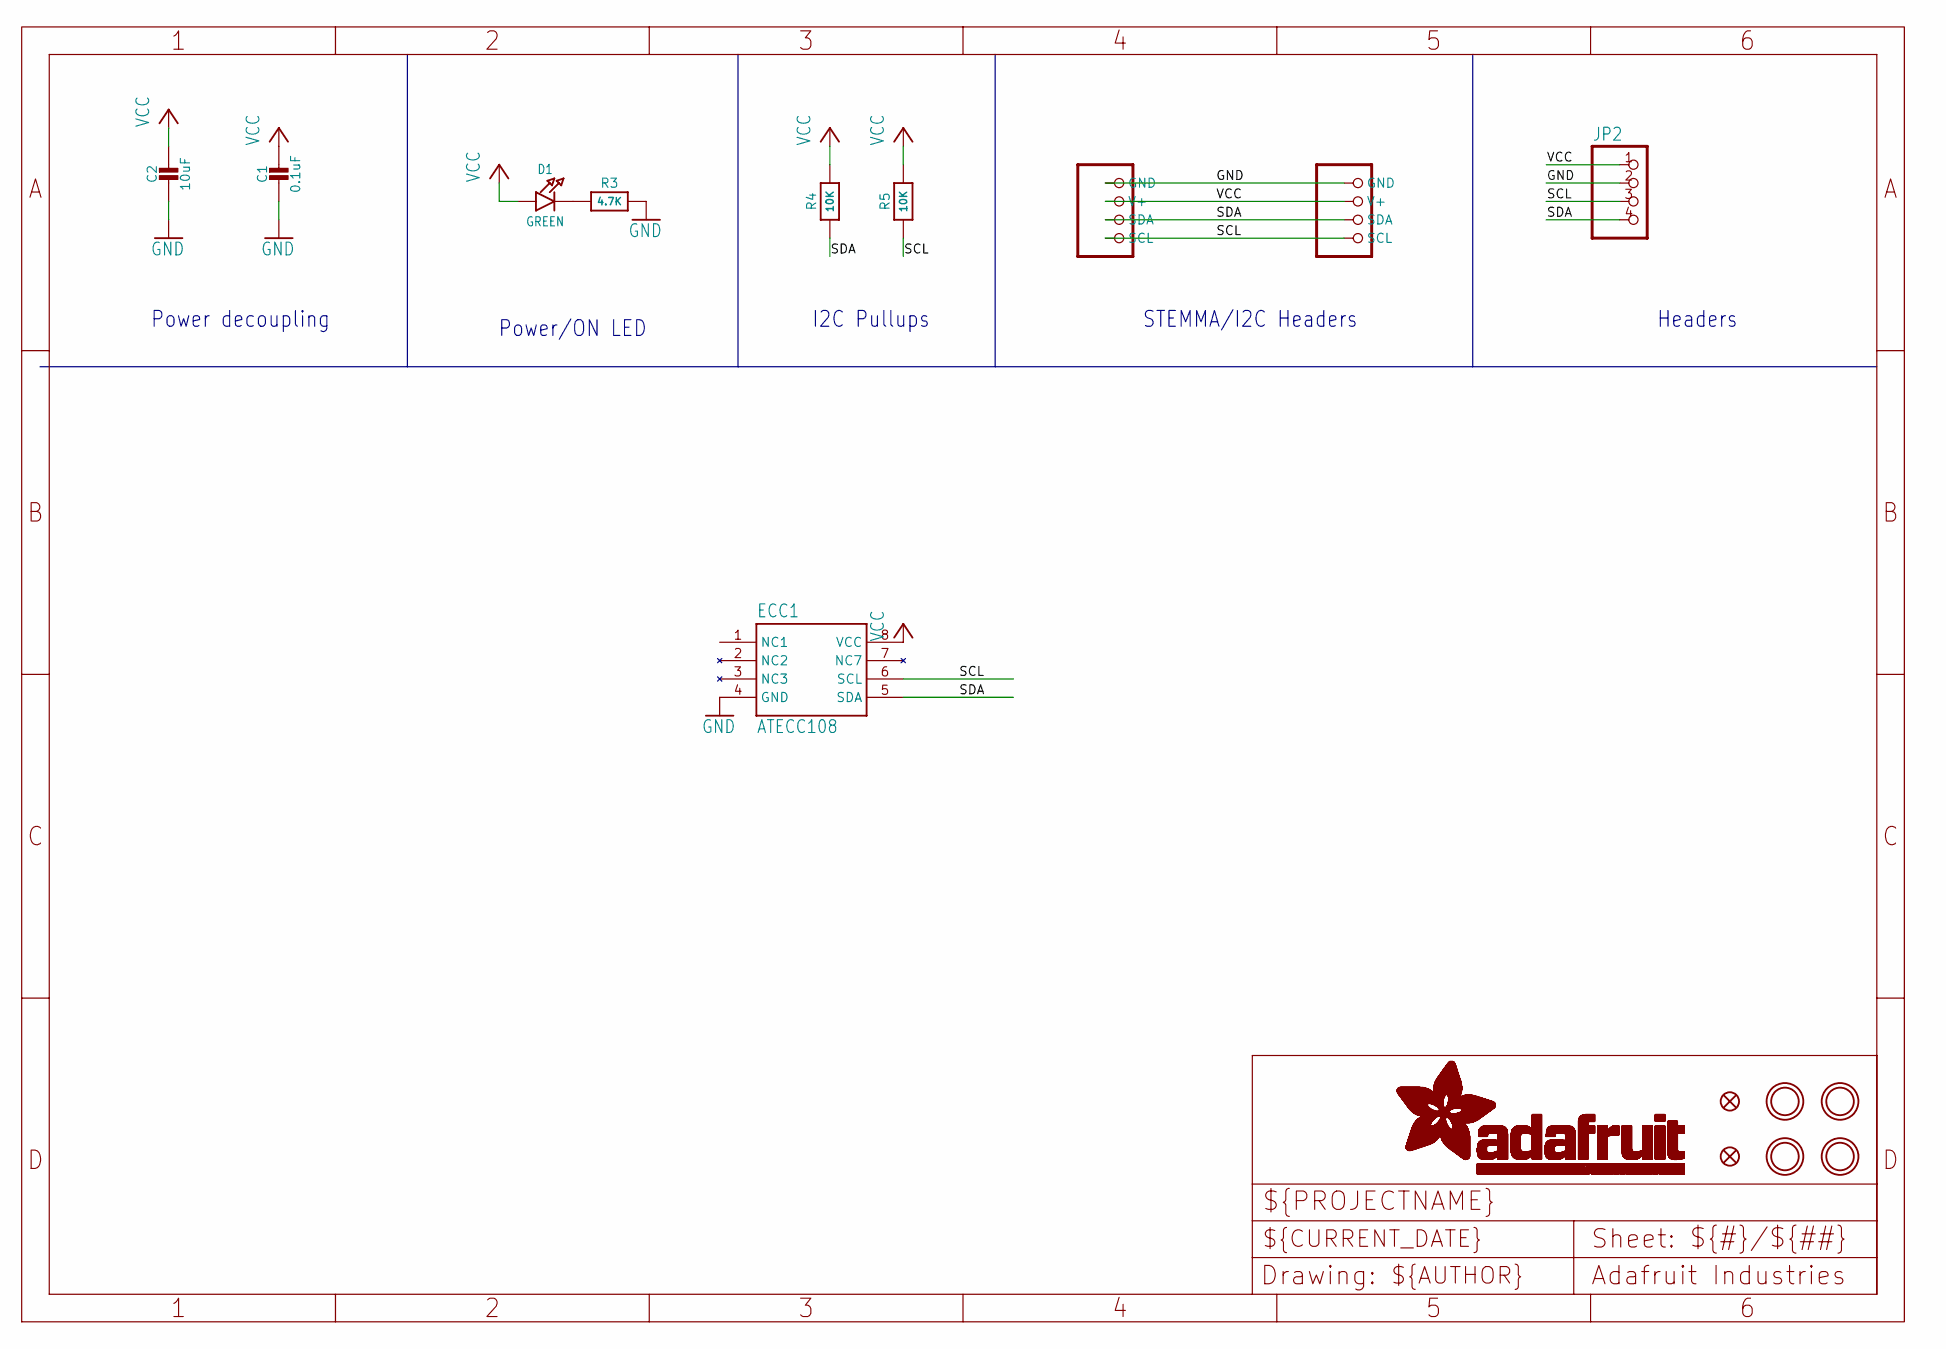
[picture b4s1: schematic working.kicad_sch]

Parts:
C1: 0.1uF; 0603-NO
C2: 10uF; 0805-NO
CONN3, CONN4: STEMMA_I2C_QT; JST_SH4
D1: GREEN; CHIPLED_0603_NOOUTLINE
ECC1: ATECC108; SOIC8
FID3, FID4: FIDUCIAL_1MM
JP2: HEADER-1X4ROUND; 1X04_ROUND
R3: 4.7K; 0603-NO
R4, R5: 10K; 0603-NO
U$11, U$12, U$14, U$15: MOUNTINGHOLE2.5; MOUNTINGHOLE_2.5_PLATED

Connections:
GND: C1.2, C2.2, CONN3.1 (GND), CONN4.1 (GND), ECC1.4 (GND), JP2.2, R3.2
unnamed: D1.C, R3.1
SCL: CONN3.4 (SCL), CONN4.4 (SCL), ECC1.6 (SCL), JP2.3, R5.1
SDA: CONN3.3 (SDA), CONN4.3 (SDA), ECC1.5 (SDA), JP2.4, R4.1
VCC: C1.1, C2.1, CONN3.2 (V+), CONN4.2 (V+), D1.A, ECC1.8 (VCC), JP2.1, R4.2, R5.2

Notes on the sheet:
I2C Pullups
Power decoupling
Power/ON LED
Headers
STEMMA/I2C Headers

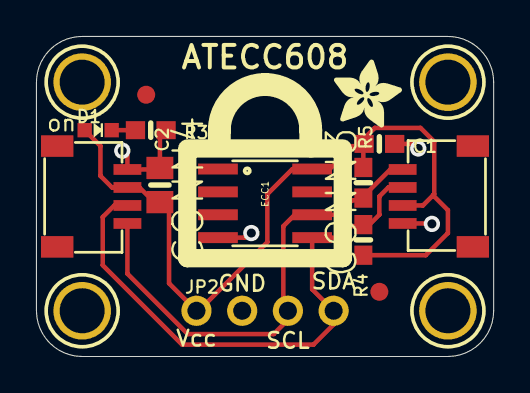
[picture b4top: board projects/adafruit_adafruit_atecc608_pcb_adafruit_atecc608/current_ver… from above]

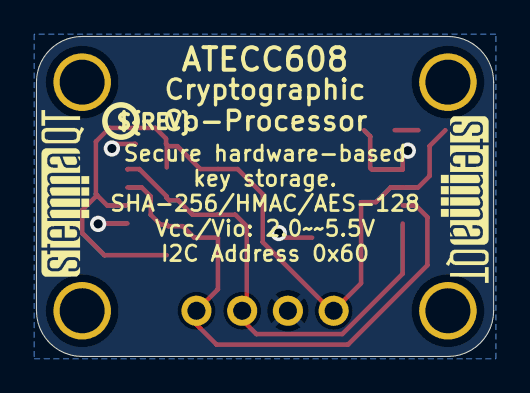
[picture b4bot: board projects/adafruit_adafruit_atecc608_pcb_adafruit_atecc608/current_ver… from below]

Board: 2 copper layers, 25.4 x 17.8 mm, 20 parts (3 on the bottom side), 5 nets.

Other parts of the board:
U$17: ADAFRUIT_3.5MM
U$18: PCBFEAT-REV-040
U$19, U$20: STEMMAQT

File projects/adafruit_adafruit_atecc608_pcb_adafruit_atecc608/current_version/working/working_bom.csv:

"Id";"Designator";"Footprint";"Quantity";"Designation";"Supplier and ref";
1;"U$12,U$11,U$14,U$15";"MOUNTINGHOLE_2.5_PLATED";4;"MOUNTINGHOLE2.5";;;
2;"JP2";"1X04_ROUND";1;"";;;
3;"U$17";"ADAFRUIT_3.5MM";1;"";;;
4;"FID4,FID3";"FIDUCIAL_1MM";2;"FIDUCIAL_1MM";;;
5;"ECC1";"SOIC8";1;"ATECC608";;;
6;"R3";"0603-NO";1;"4.7K";;;
7;"R4,R5";"0603-NO";2;"10K";;;
8;"C2";"0805-NO";1;"10uF";;;
9;"D1";"CHIPLED_0603_NOOUTLINE";1;"GREEN";;;
10;"CONN4,CONN3";"JST_SH4";2;"STEMMA_I2C_QT";;;
11;"C1";"0603-NO";1;"0.1uF";;;
12;"U$20,U$19";"STEMMAQT";2;"";;;
13;"U$18";"PCBFEAT-REV-040";1;"";;;
